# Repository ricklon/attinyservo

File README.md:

attinyservo
===========

Attiny Servo Board can easily be pogrammed by Arduino as ISP, and Arduino API

The through hole version is in the pth directory. The surface mount version is in the smt directory.

Arduino Core
====
* Attiny Core Google, https://code.google.com/p/arduino-tiny/
* Hi Tech LoTech Core, http://hlt.media.mit.edu/?p=1695
* 

Servo
====
* Servo Library: https://github.com/fri000/Servo8Bit
* Installation: http://www.cunningturtle.com/servo8bit-library-version-0-6-released/

Social Hardware:
=====
* Open Source
* Open Hardware
* Sharable

Licensing
====
The AttinyServo hardware is licenced under the Solderpad Hardware License v0.5.

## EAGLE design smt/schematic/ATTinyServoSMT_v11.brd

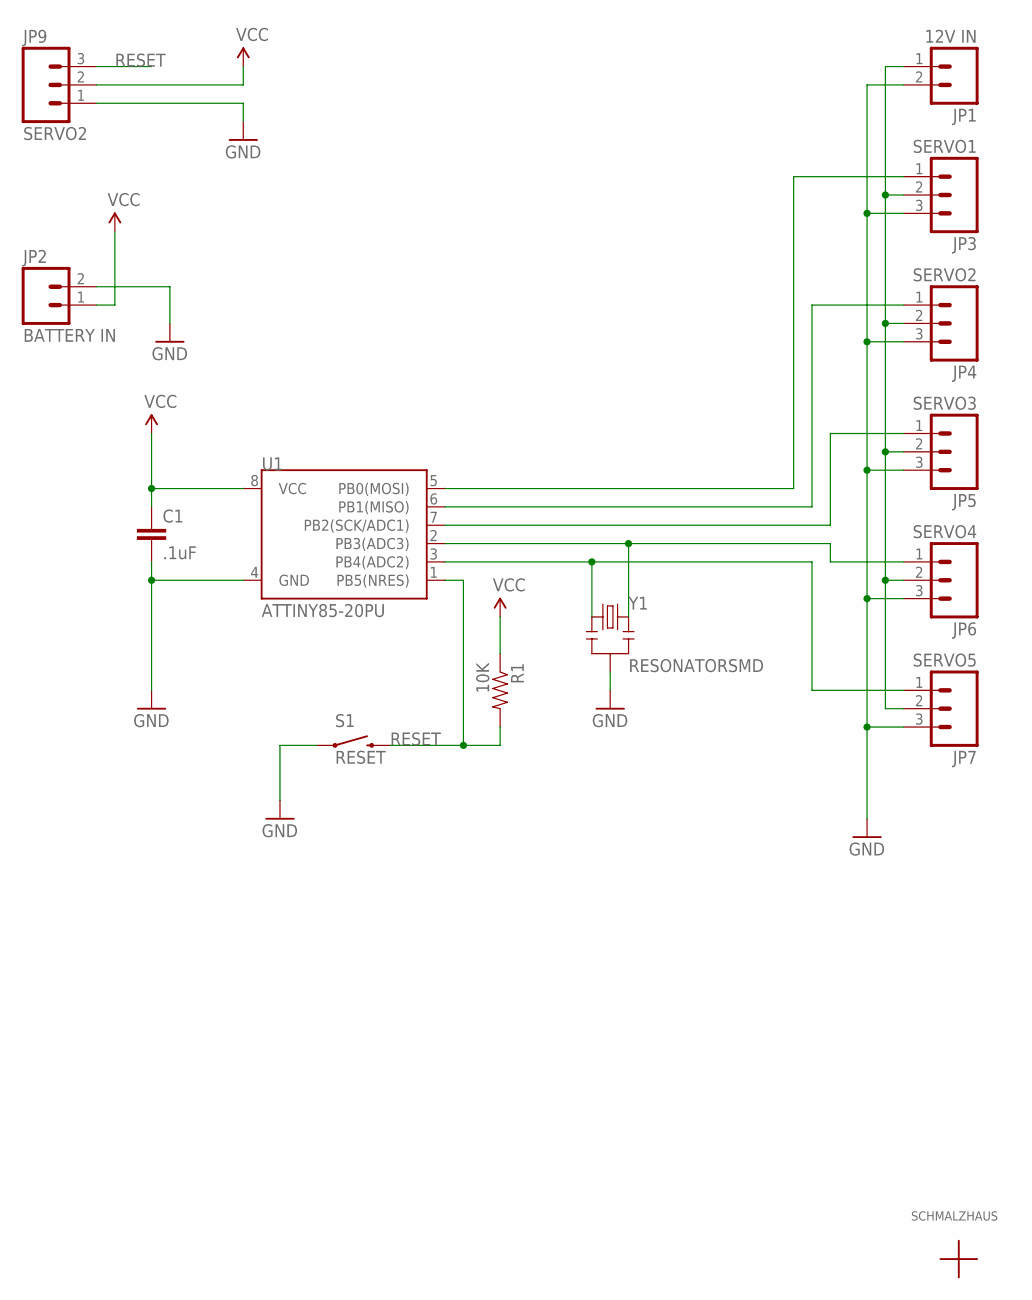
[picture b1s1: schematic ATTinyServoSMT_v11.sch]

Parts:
C1: .1uF; 0603-CAP
JP1: 12V IN; SCREWTERMINAL-3.5MM-2
JP2: BATTERY IN; SCREWTERMINAL-3.5MM-2
JP3: SERVO1; 1X03
JP4, JP9: SERVO2; 1X03
JP5: SERVO3; 1X03
JP6: SERVO4; 1X03
JP7: SERVO5; 1X03
R1: 10K; 0603-RES
S1: RESET; TACTILE_SWITCH_SMD
U1: ATTINY85-20PU; SO08-EIAJ
U$1: SCHMALZHAUSSCHMALZHAUS_SMALL; SCHMALZHAUS_SMALL
Y1: RESONATORSMD; RESONATOR-SMD

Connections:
GND: C1.2, JP1.2, JP2.2, JP3.3, JP4.3, JP5.3, JP6.3, JP7.3, JP9.1, S1.1, U1.4 (GND), Y1.2
unnamed: JP1.1, JP3.2, JP4.2, JP5.2, JP6.2, JP7.2
unnamed: JP6.1, U1.2 (PB3(ADC3)), Y1.3
unnamed: JP7.1, U1.3 (PB4(ADC2)), Y1.1
unnamed: JP5.1, U1.7 (PB2(SCK/ADC1))
unnamed: JP4.1, U1.6 (PB1(MISO))
unnamed: JP3.1, U1.5 (PB0(MOSI))
RESET: JP9.3, R1.2, S1.3 (2), U1.1 (PB5(NRES))
VCC: C1.1, JP2.1, JP9.2, R1.1, U1.8 (VCC)

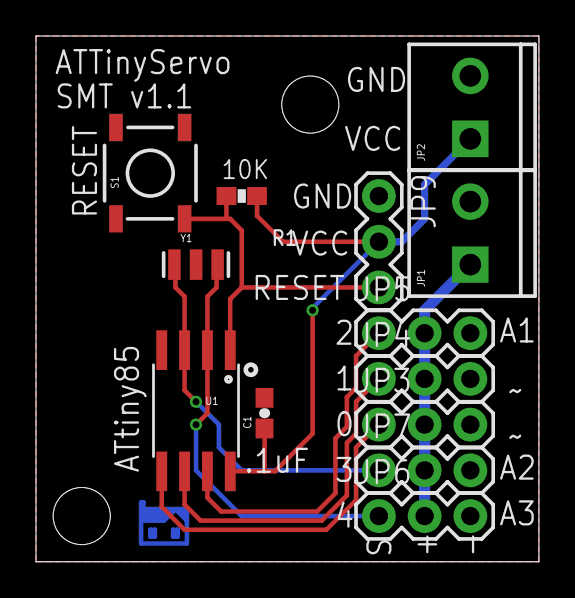
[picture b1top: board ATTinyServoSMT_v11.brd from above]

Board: 2 copper layers, 27.9 x 29.2 mm, 14 parts (1 on the bottom side), 9 nets.

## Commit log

2012-12-19 Starter files added to project. In this version GND, Vcc reversed for chip power. Arduino ISP programming for the board shown in programming folder.
2012-12-19 added the image of the Fritzing file showing the wiring to program.
2013-03-06 Added programming, packaging, updated through hole version, and new smt version.
2013-03-06 Added the test gerbers, and sample image file.
2013-03-06 Reorganized the gerber files.
2013-03-07 Updated the images, and regenerated the gerbers -tNames layer.
2013-03-07 updated and added the gerbers directory.
2013-03-10 Fixed the Fritzing, and Image to have the reset pin connected by the capacitor. This prevents the Arduino from reseting when the reset for the Attiny85 is sent via ArduinoISP.
2013-03-11 Update pins 3,4 to map correct to A2, A3.
2013-03-15 updated verisons and gerbers.
2014-11-07 Updated the Fritizing file. Added mega configuration.
2014-11-07 updated the mega fritzing.

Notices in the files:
parts and their libraries:
SparkFun: Licensing: CC v3.0 Share-Alike You are welcome to use this library for commercial purposes.
